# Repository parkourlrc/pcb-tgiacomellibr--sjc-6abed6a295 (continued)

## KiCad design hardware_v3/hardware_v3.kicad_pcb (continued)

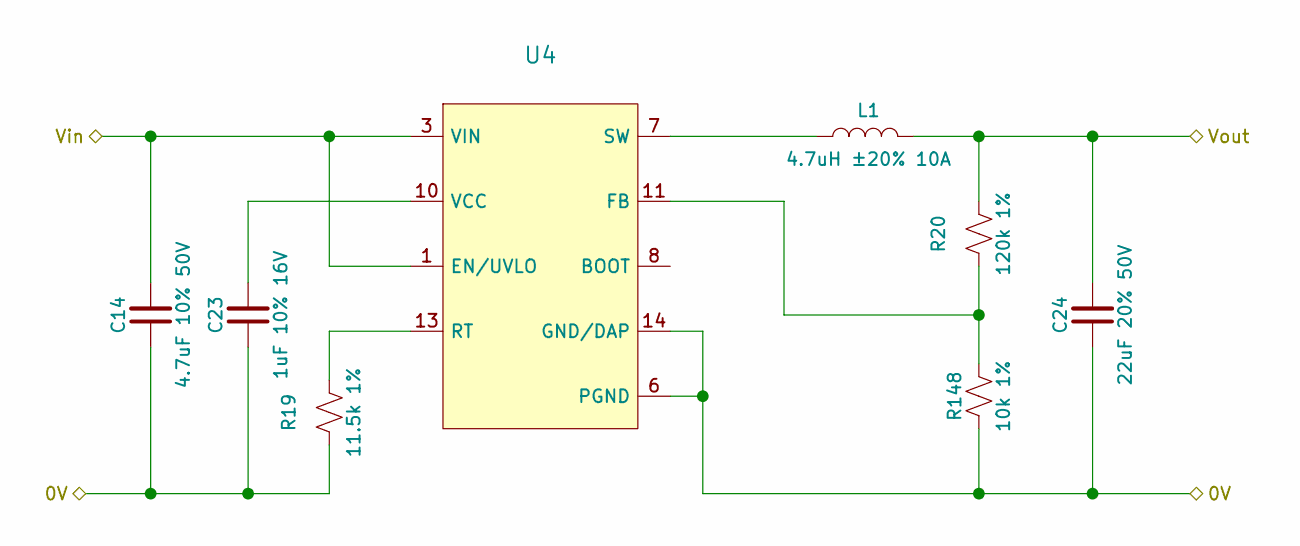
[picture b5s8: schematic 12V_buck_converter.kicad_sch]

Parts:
C14: 4.7uF 10% 50V; C_1206_3216Metric_Pad1.33x1.80mm_HandSolder; JLCPCB Part # C77096
C23: 1uF 10% 16V; C_0603_1608Metric_Pad1.08x0.95mm_HandSolder; JLCPCB Part # C92759
C24: 22uF 20% 50V; C_2220_5750Metric; JLCPCB Part # C2178233
L1: 4.7uH ±20% 10A; L_Vishay_IHLP-5050; JLCPCB Part # C845092
R19: 11.5k 1%; R_0603_1608Metric_Pad0.98x0.95mm_HandSolder; JLCPCB Part # C100728
R20: 120k 1%; R_0603_1608Metric_Pad0.98x0.95mm_HandSolder; JLCPCB Part # C114607
R148: 10k 1%; R_0603_1608Metric; JLCPCB Part # C98220
U4: (no value)

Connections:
+12V: C24.2, L1.2, R20.2; also elsewhere on the board
/Power Supply/12V_buck_converter/Vin: C14.2, U4.1 (EN/UVLO), U4.3 (VIN); also elsewhere on the board
unnamed: R20.1, R148.2, U4.11 (FB)
unnamed: U4.2 (NC), U4.4 (NC), U4.5 (NC), U4.9 (NC), U4.12 (NC)
unnamed: R19.2, U4.13 (RT)
unnamed: L1.1, U4.7 (SW)
unnamed: C23.2, U4.10 (VCC)
PGND: C14.1, C23.1, C24.1, R19.1, R148.1, U4.6 (PGND), U4.14 (GND/DAP); also elsewhere on the board

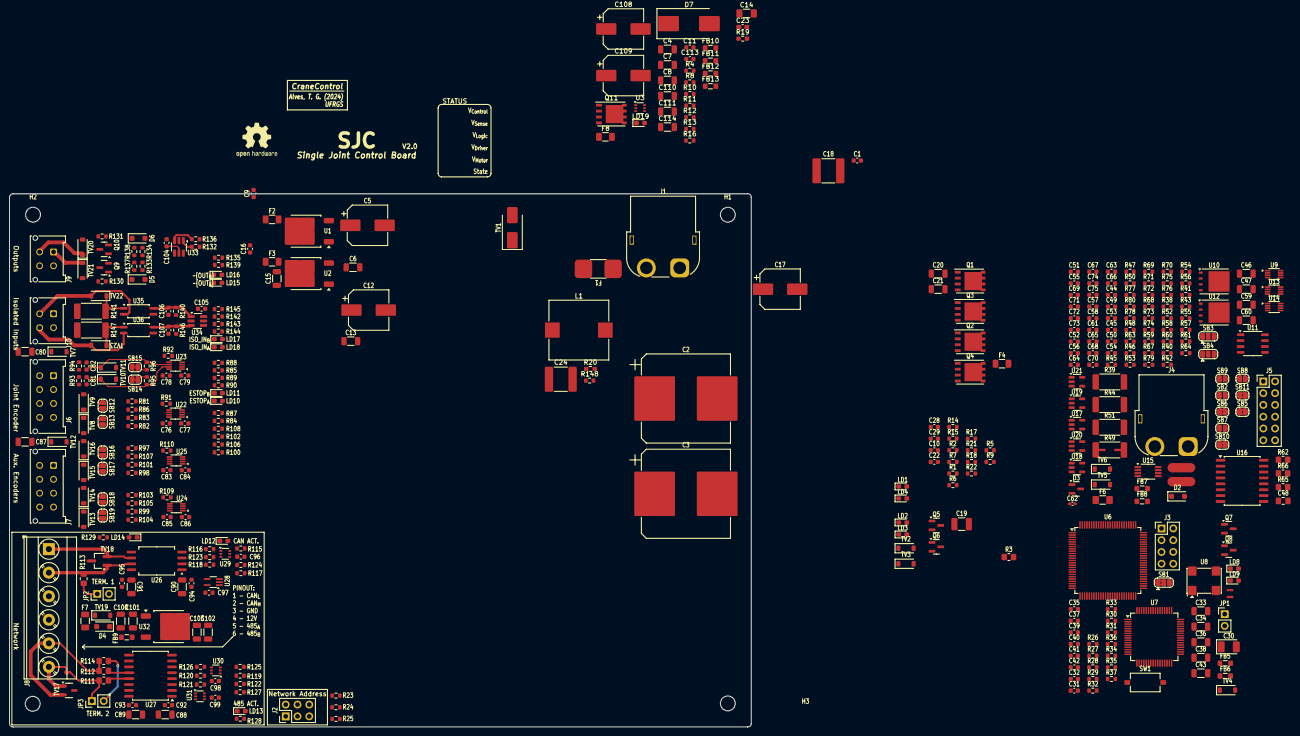
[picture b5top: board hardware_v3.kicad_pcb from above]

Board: 4 copper layers, 160.0 x 115.0 mm, 407 parts (0 on the bottom side), 255 nets.

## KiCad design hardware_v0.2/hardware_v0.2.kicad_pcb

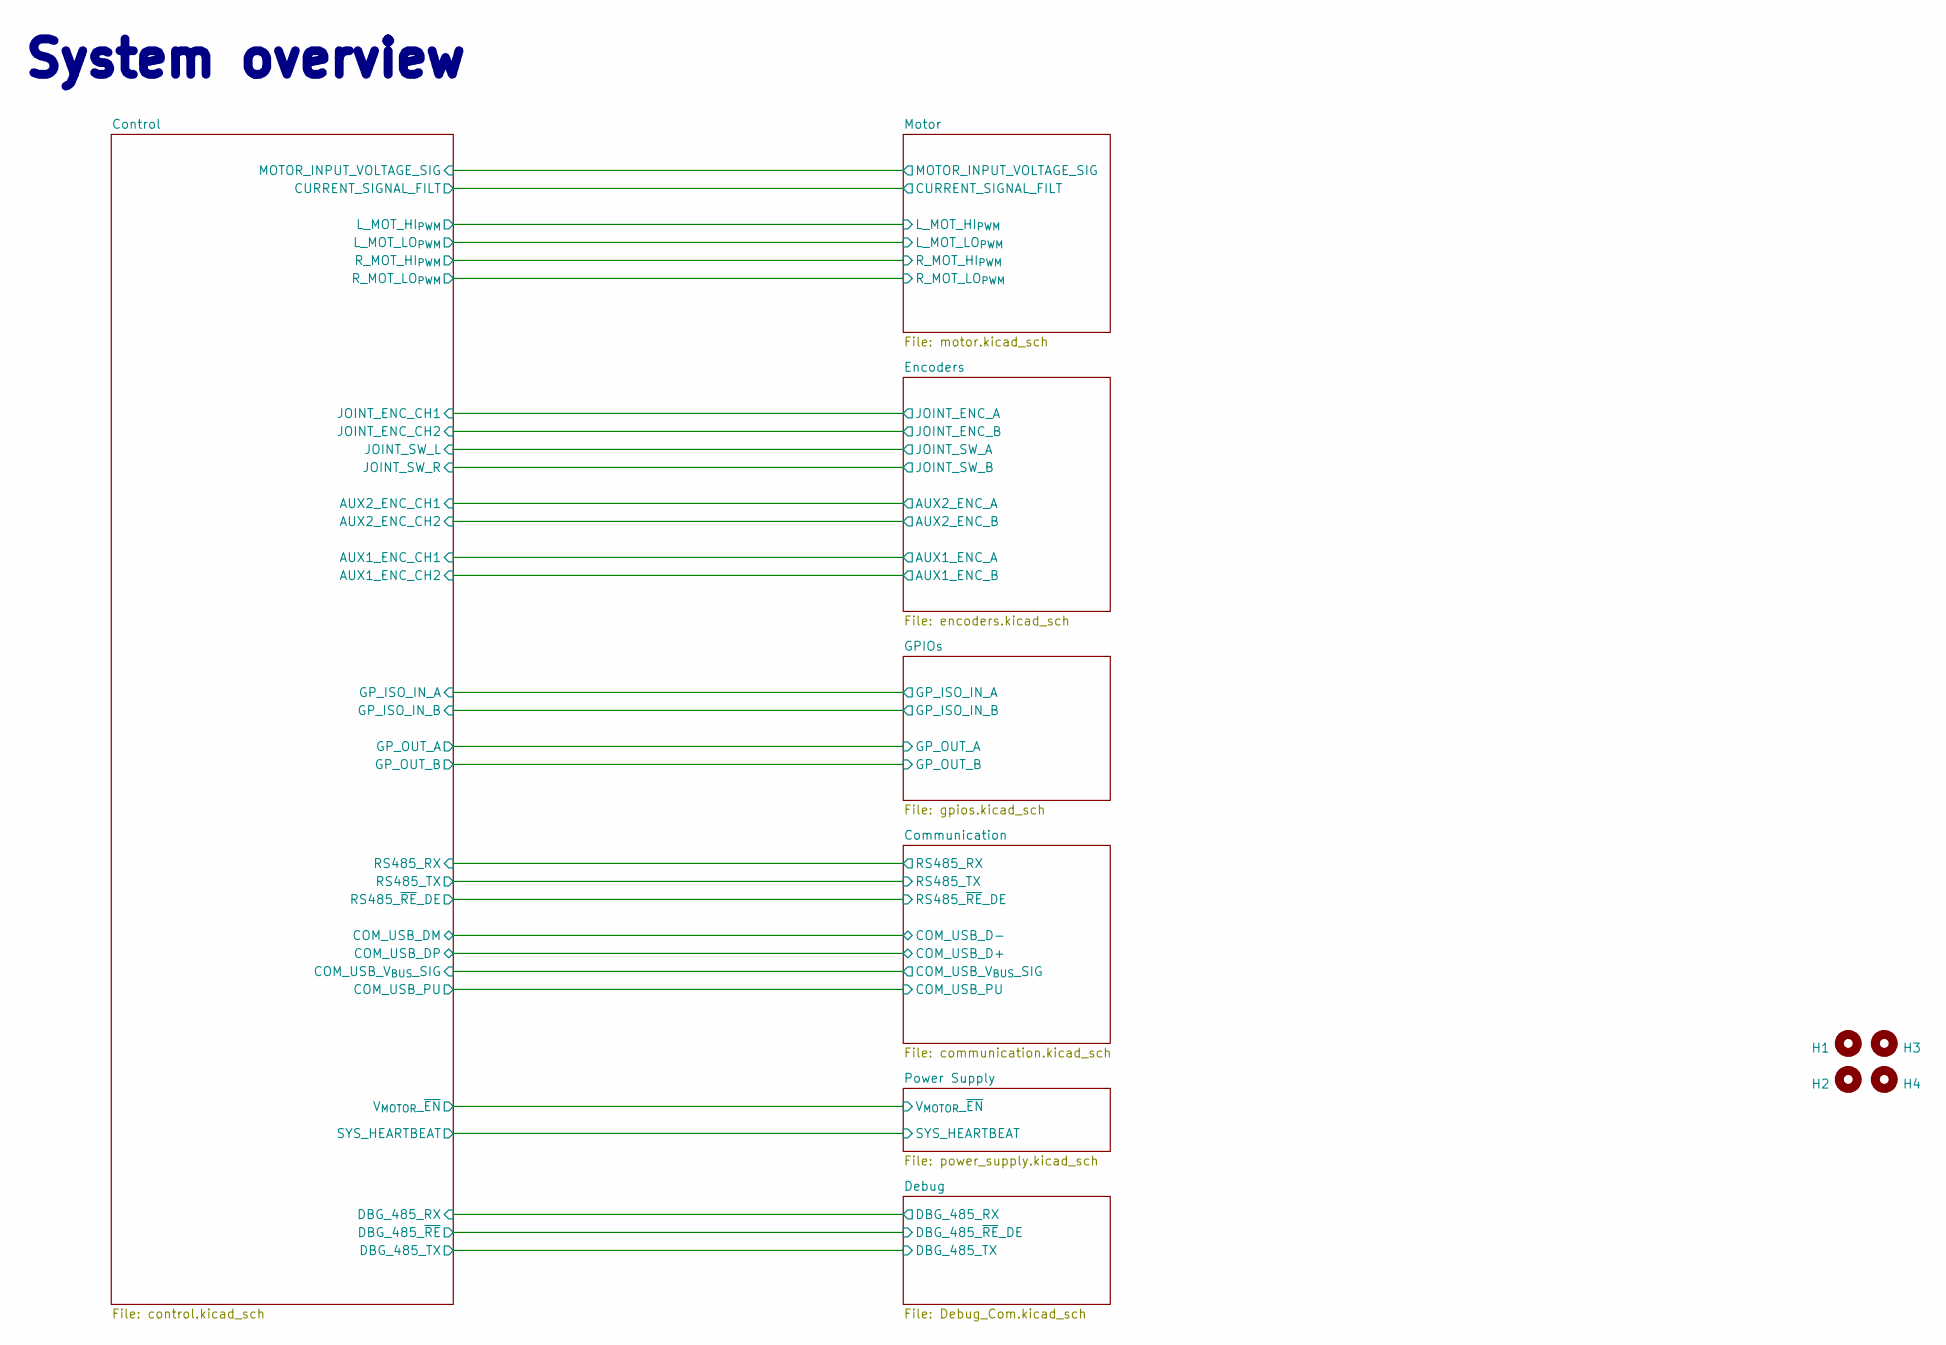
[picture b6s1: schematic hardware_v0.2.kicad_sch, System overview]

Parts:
H1, H2, H3, H4: MountingHole; MountingHole_3.2mm_M3_ISO7380

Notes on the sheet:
System overview

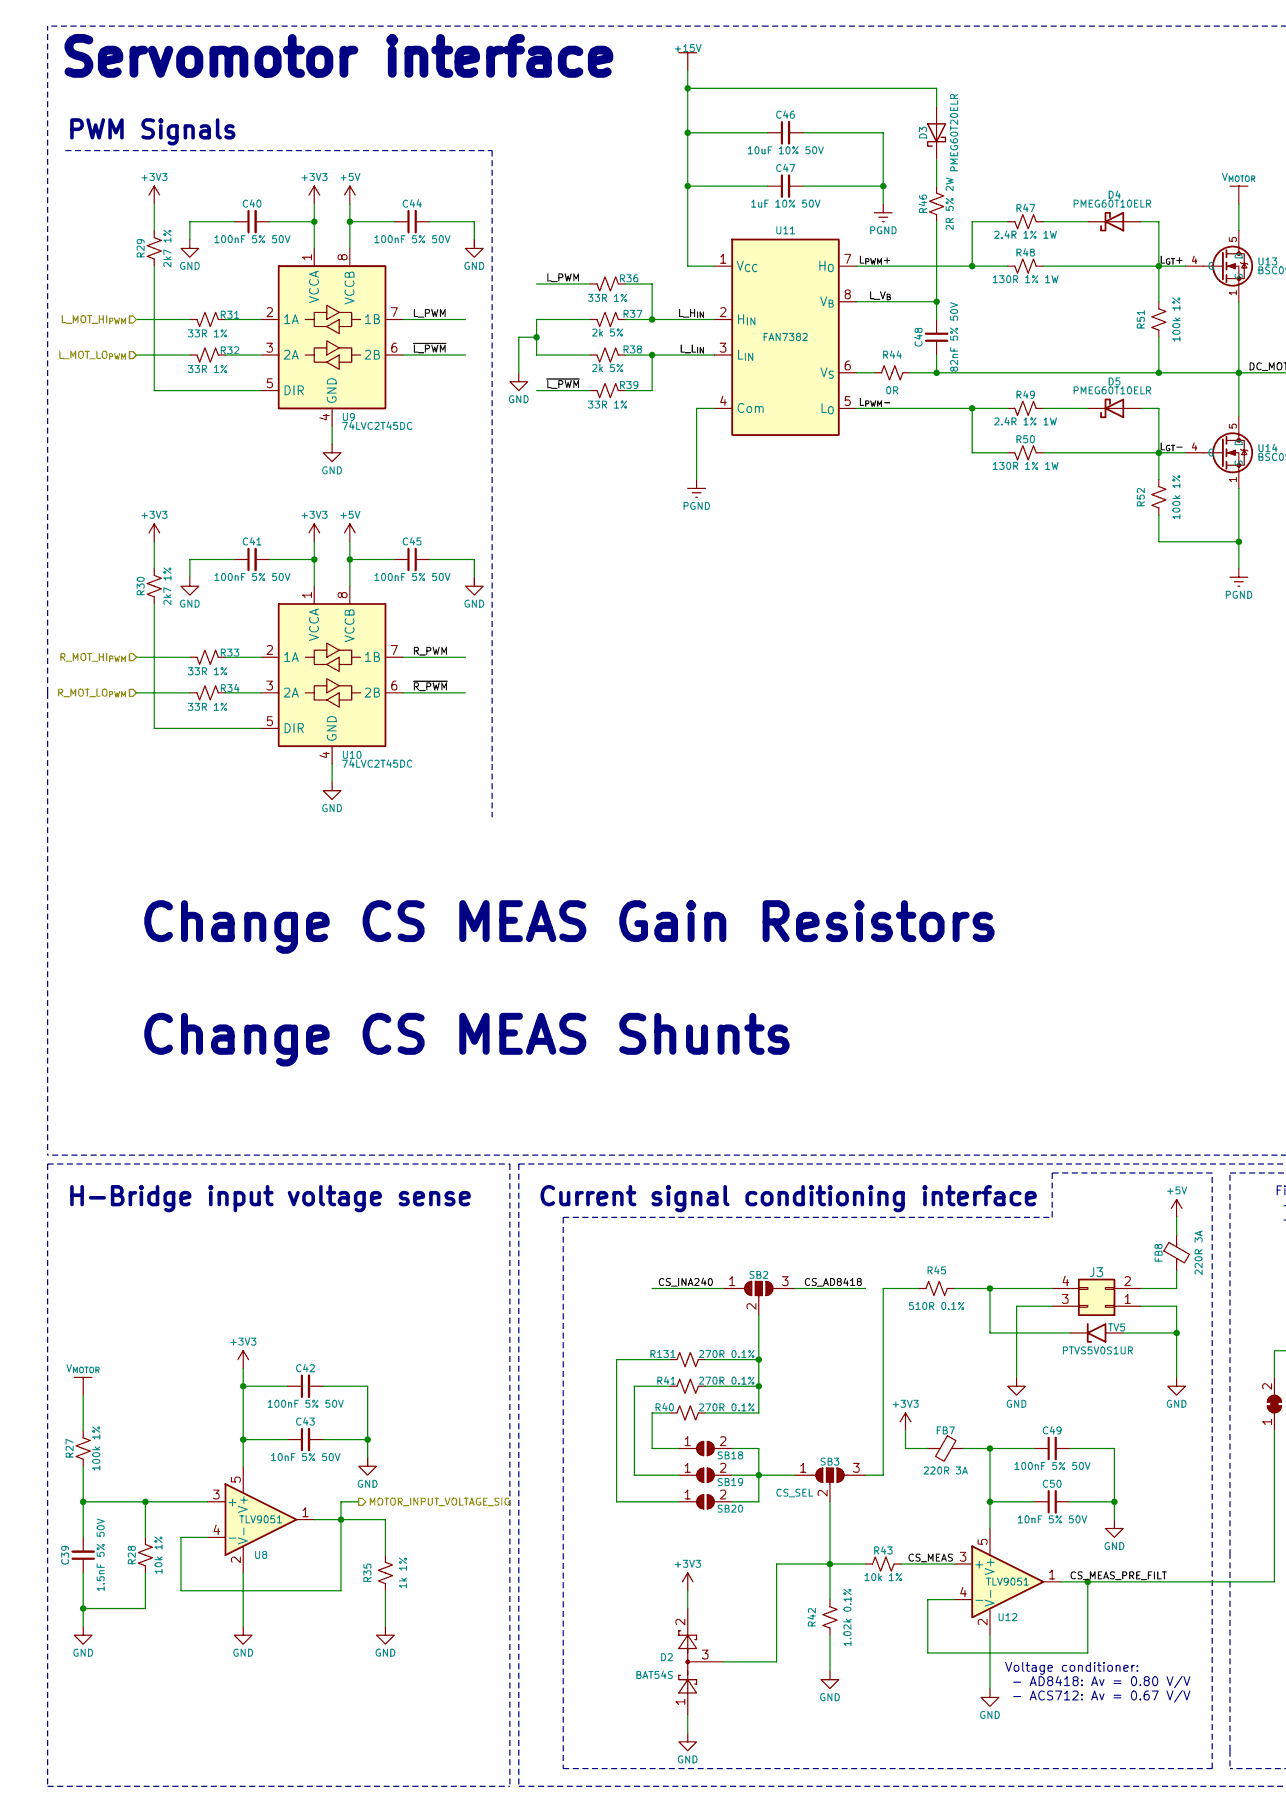
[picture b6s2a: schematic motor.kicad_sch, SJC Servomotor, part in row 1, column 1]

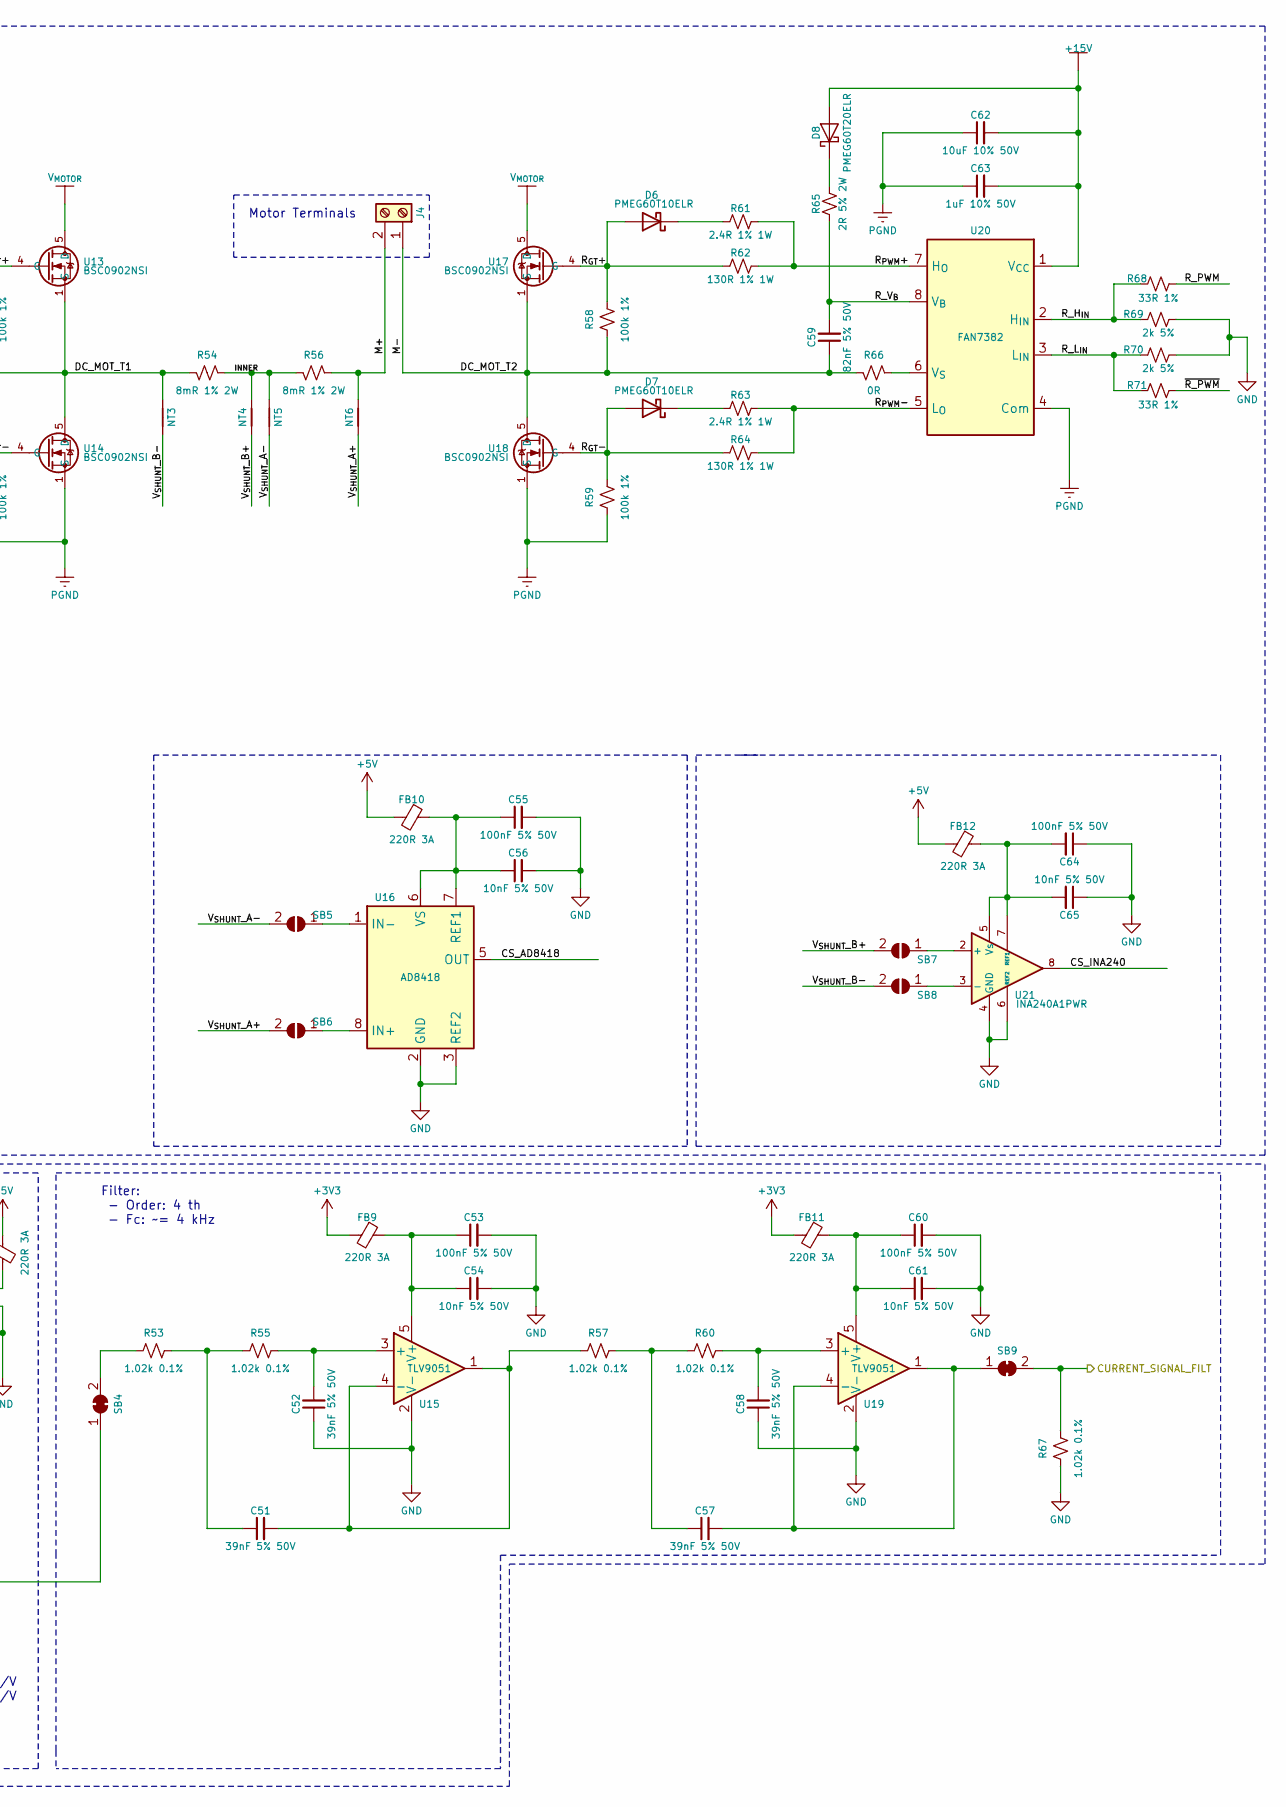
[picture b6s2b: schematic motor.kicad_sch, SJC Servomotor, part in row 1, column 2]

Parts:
C39: 1.5nF 5% 50V; C_0603_1608Metric; JLCPCB Part # C107039
C40, C41, C42, C44, C45, C49, C53, C55, C60, C64: 100nF 5% 50V; C_0603_1608Metric; JLCPCB Part # C91183
C43, C50, C54, C56, C61, C65: 10nF 5% 50V; C_0603_1608Metric; JLCPCB Part # C389113
C46, C62: 10uF 10% 50V; C_1206_3216Metric; JLCPCB Part # C13585
C47, C63: 1uF 10% 50V; C_1206_3216Metric; JLCPCB Part # C1848
C48, C59: 82nF 5% 50V; C_0805_2012Metric_Pad1.18x1.45mm_HandSolder; JLCPCB Part # C520047
C51, C52, C57, C58: 39nF 5% 50V; C_0603_1608Metric; JLCPCB Part # C519553
D2: BAT54S; SOT-23; JLCPCB Part # C19726
D3, D8: PMEG60T20ELR; D_SOD-123F; JLCPCB Part # C552947
D4, D5, D6, D7: PMEG60T10ELR; D_SOD-123F; JLCPCB Part # C552945
FB7, FB8, FB9, FB10, FB11, FB12: 220R 3A; L_0805_2012Metric_Pad1.05x1.20mm_HandSolder; JLCPCB Part # C76818
J3: Debug-485; PinHeader_2x02_P2.54mm_Vertical
J4: Motor; AMASS_XT60PW-M_1x02_P7.20mm_Horizontal; JLCPCB Part # C98732
NT3, NT5: SHUNT IN-; NetTie-2_SMD_Pad1.0mm
NT4, NT6: SHUNT IN+; NetTie-2_SMD_Pad1.0mm
R27, R51, R52, R58, R59: 100k 1%; R_0603_1608Metric; JLCPCB Part # C14675
R28, R43: 10k 1%; R_0603_1608Metric; JLCPCB Part # C98220
R29, R30: 2k7 1%; R_0603_1608Metric; JLCPCB Part # C114612
R31, R32, R33, R34, R36, R39, R68, R71: 33R 1%; R_0603_1608Metric; JLCPCB Part # C108661
R35: 1k 1%; R_0603_1608Metric; JLCPCB Part # C22548
R37, R38, R69, R70: 2k 5%; R_0603_1608Metric; JLCPCB Part # C103396
R40, R41, R131: 270R 0.1%; R_0603_1608Metric; JLCPCB Part # C861270
R42, R53, R55, R57, R60, R67: 1.02k 0.1%; R_0603_1608Metric; JLCPCB Part # C705819
R44, R66: 0R; R_0603_1608Metric; JLCPCB Part # C103196
R45: 510R 0.1%; R_0603_1608Metric; JLCPCB Part # C2828640
R46, R65: 2R 5% 2W; R_2512_6332Metric_Pad1.40x3.35mm_HandSolder; JLCPCB Part # C91926
R47, R49, R61, R63: 2.4R 1% 1W; R_2512_6332Metric_Pad1.40x3.35mm_HandSolder; JLCPCB Part # C175225
R48, R50, R62, R64: 130R 1% 1W; R_2512_6332Metric_Pad1.40x3.35mm_HandSolder; JLCPCB Part # C728111
R54, R56: 8mR 1% 2W; R_2512_6332Metric_Pad1.40x3.35mm_HandSolder; JLCPCB Part # C2440282
SB2, SB3: CS_SEL; SolderJumper-3_P1.3mm_Open_RoundedPad1.0x1.5mm
SB4, SB9: SolderJumper-2_P1.3mm_Bridged2Bar_RoundedPad1.0x1.5mm
SB5, SB6, SB7, SB8, SB18, SB19, SB20: SolderJumper-2_P1.3mm_Open_RoundedPad1.0x1.5mm
TV5: PTVS5V0S1UR; D_SOD-123; JLCPCB Part # C478011
U8, U12, U15, U19: TLV9051; SOT-23-5; JLCPCB Part # C1849429
U9, U10: 74LVC2T45DC; VSSOP-8_2.3x2mm_P0.5mm; JLCPCB Part # C730237
U11, U20: FAN7382; SOIC-8_3.9x4.9mm_P1.27mm; JLCPCB Part # C128796
U13, U14, U17, U18: BSC0902NSI; TDSON-8-1; JLCPCB Part # C534382
U16: AD8418; MSOP-8_3x3mm_P0.65mm; JLCPCB Part # C147928
U21: INA240A1PWR; TSSOP-8_4.4x3mm_P0.65mm; JLCPCB Part # C93965

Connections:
+3V3: C40.2, C41.2, C42.1, C43.1, D2.2, FB7.2, FB9.2, FB11.2, R29.2, R30.2, U8.5 (V+), U9.1 (VCCA), U10.1 (VCCA); also elsewhere on the board
+5V: C44.1, C45.1, FB8.1, FB10.2, FB12.2, U9.8 (VCCB), U10.8 (VCCB); also elsewhere on the board
+15V: C46.1, C47.1, C62.2, C63.2, D3.2 (A), D8.2 (A), U11.1 (V_{CC}), U20.1 (V_{CC}); also elsewhere on the board
/Control/CURRENT_SIGNAL_FILT: R67.2, SB9.2 (B); also elsewhere on the board
/Control/L_MOT_HI_{PWM}: R31.2; also elsewhere on the board
/Control/L_MOT_LO_{PWM}: R32.2; also elsewhere on the board
/Control/MOTOR_INPUT_VOLTAGE_SIG: R35.2, U8.1, U8.4 (-); also elsewhere on the board
/Control/R_MOT_HI_{PWM}: R33.2; also elsewhere on the board
/Control/R_MOT_LO_{PWM}: R34.2; also elsewhere on the board
/Motor/CS_MEAS: R43.2, U12.3 (+)
/Motor/CS_MEAS_PRE_FILT: SB4.1 (A), U12.1, U12.4 (-)
/Motor/DC_MOT_T1: C48.1, NT3.1, R44.2, R51.1, R54.2, U13.1 (S), U13.2 (S), U13.3 (S), U14.5 (D)
/Motor/DC_MOT_T2: C59.1, J4.1, R58.1, R66.2, U17.1 (S), U17.2 (S), U17.3 (S), U18.5 (D)
/Motor/INNER: NT4.1, NT5.1, R54.1, R56.2
/Motor/L_H_{IN}: R36.1, R37.1, U11.2 (H_{IN})
/Motor/L_L_{IN}: R38.1, R39.1, U11.3 (L_{IN})
/Motor/L_PWM: R36.2, U9.7 (1B)
/Motor/L_V_{B}: C48.2, R46.1, U11.8 (V_{B})
/Motor/L_{GT}+: D4.2 (A), R48.1, R51.2, U13.4 (G)
/Motor/L_{GT}-: D5.2 (A), R50.1, R52.2, U14.4 (G)
/Motor/L_{PWM}+: R47.2, R48.2, U11.7 (H_{O})
/Motor/L_{PWM}-: R49.2, R50.2, U11.5 (L_{O})
/Motor/M+: J4.2, NT6.1, R56.1
/Motor/R_H_{IN}: R68.1, R69.1, U20.2 (H_{IN})
/Motor/R_L_{IN}: R70.1, R71.1, U20.3 (L_{IN})
/Motor/R_PWM: R68.2, U10.7 (1B)
/Motor/R_V_{B}: C59.2, R65.1, U20.8 (V_{B})
/Motor/R_{GT}+: D6.2 (A), R58.2, R62.1, U17.4 (G)
/Motor/R_{GT}-: D7.2 (A), R59.2, R64.1, U18.4 (G)
/Motor/R_{PWM}+: R61.2, R62.2, U20.7 (H_{O})
/Motor/R_{PWM}-: R63.2, R64.2, U20.5 (L_{O})
/Motor/V_{SHUNT}_B+: NT4.2, SB7.1 (A), SB7.2 (B), U21.2 (+)
/Motor/V_{SHUNT}_B-: NT3.2, SB8.1 (A), SB8.2 (B), U21.3 (-)
/Motor/~L_PWM: R39.2, U9.6 (2B)
/Motor/~R_PWM: R71.2, U10.6 (2B)
GND: C39.1, C40.1, C41.1, C42.2, C43.2, C44.2, C45.2, C49.2, C50.2, C52.1, C53.2, C54.2, C55.2, C56.2, C58.1, C60.2, C61.2, C64.1, C65.1, D2.1, J3.1, J3.3, R28.1, R35.1, R37.2, R38.2, R42.1, R67.1, R69.2, R70.2, TV5.2 (A), U8.2 (V-), U9.4 (GND), U10.4 (GND), U12.2 (V-), U15.2 (V-), U16.2 (GND), U16.3 (REF2), U19.2 (V-), U21.1 (GND), U21.4 (GND), U21.6 (REF2); also elsewhere on the board
unnamed: C51.1, R53.2, R55.1
unnamed: C57.1, R57.2, R60.1
unnamed: D3.1 (K), R46.2
unnamed: D4.1 (K), R47.1
unnamed: D5.1 (K), R49.1
unnamed: D6.1 (K), R61.1
unnamed: D7.1 (K), R63.1
unnamed: D8.1 (K), R65.2
unnamed: FB8.2, J3.2
unnamed: J3.4, R45.2, TV5.1 (K)
unnamed: R40.1, R41.1, R131.1, SB2.2 (C)
unnamed: R45.1, SB3.3 (B)
unnamed: D2.3, R42.2, R43.1, SB3.2 (C)
unnamed: R53.1, SB4.2 (B)
unnamed: C57.2, SB9.1 (A), U19.1, U19.4 (-)
unnamed: R40.2, SB18.1 (A)
unnamed: SB3.1 (A), SB18.2 (B), SB19.2 (B), SB20.2 (B)
unnamed: R41.2, SB19.1 (A)
unnamed: R131.2, SB20.1 (A)
unnamed: C39.2, R27.1, R28.2, U8.3 (+)
unnamed: R31.1, U9.2 (1A)
unnamed: R32.1, U9.3 (2A)
unnamed: R29.1, U9.5 (DIR)
unnamed: R33.1, U10.2 (1A)
unnamed: R34.1, U10.3 (2A)
unnamed: R30.1, U10.5 (DIR)
unnamed: R44.1, U11.6 (V_{S})
unnamed: C49.1, C50.1, FB7.1, U12.5 (V+)
unnamed: C52.2, R55.2, U15.3 (+)
unnamed: C51.2, R57.1, U15.1, U15.4 (-)
unnamed: C53.1, C54.1, FB9.1, U15.5 (V+)
unnamed: C55.1, C56.1, FB10.1, U16.6 (VS), U16.7 (REF1)
unnamed: C58.2, R60.2, U19.3 (+)
unnamed: C60.1, C61.1, FB11.1, U19.5 (V+)
unnamed: R66.1, U20.6 (V_{S})
unnamed: C64.2, C65.2, FB12.1, U21.5 (Vs), U21.7 (REF1)
PGND: C46.2, C47.2, C62.1, C63.1, R52.1, R59.1, U11.4 (Com), U14.1 (S), U14.2 (S), U14.3 (S), U18.1 (S), U18.2 (S), U18.3 (S), U20.4 (Com); also elsewhere on the board
V_{MOTOR}: R27.2, U13.5 (D), U17.5 (D); also elsewhere on the board

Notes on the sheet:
Current signal conditioning interface
Servomotor interface
PWM Signals
Voltage conditioner: - AD8418: Av = 0.80 V/V - ACS712: Av = 0.67 V/V
Filter: - Order: 4 th - Fc: ~= 4 kHz
Change CS MEAS Gain Resistors Change CS MEAS Shunts
Motor Terminals
H-Bridge input voltage sense

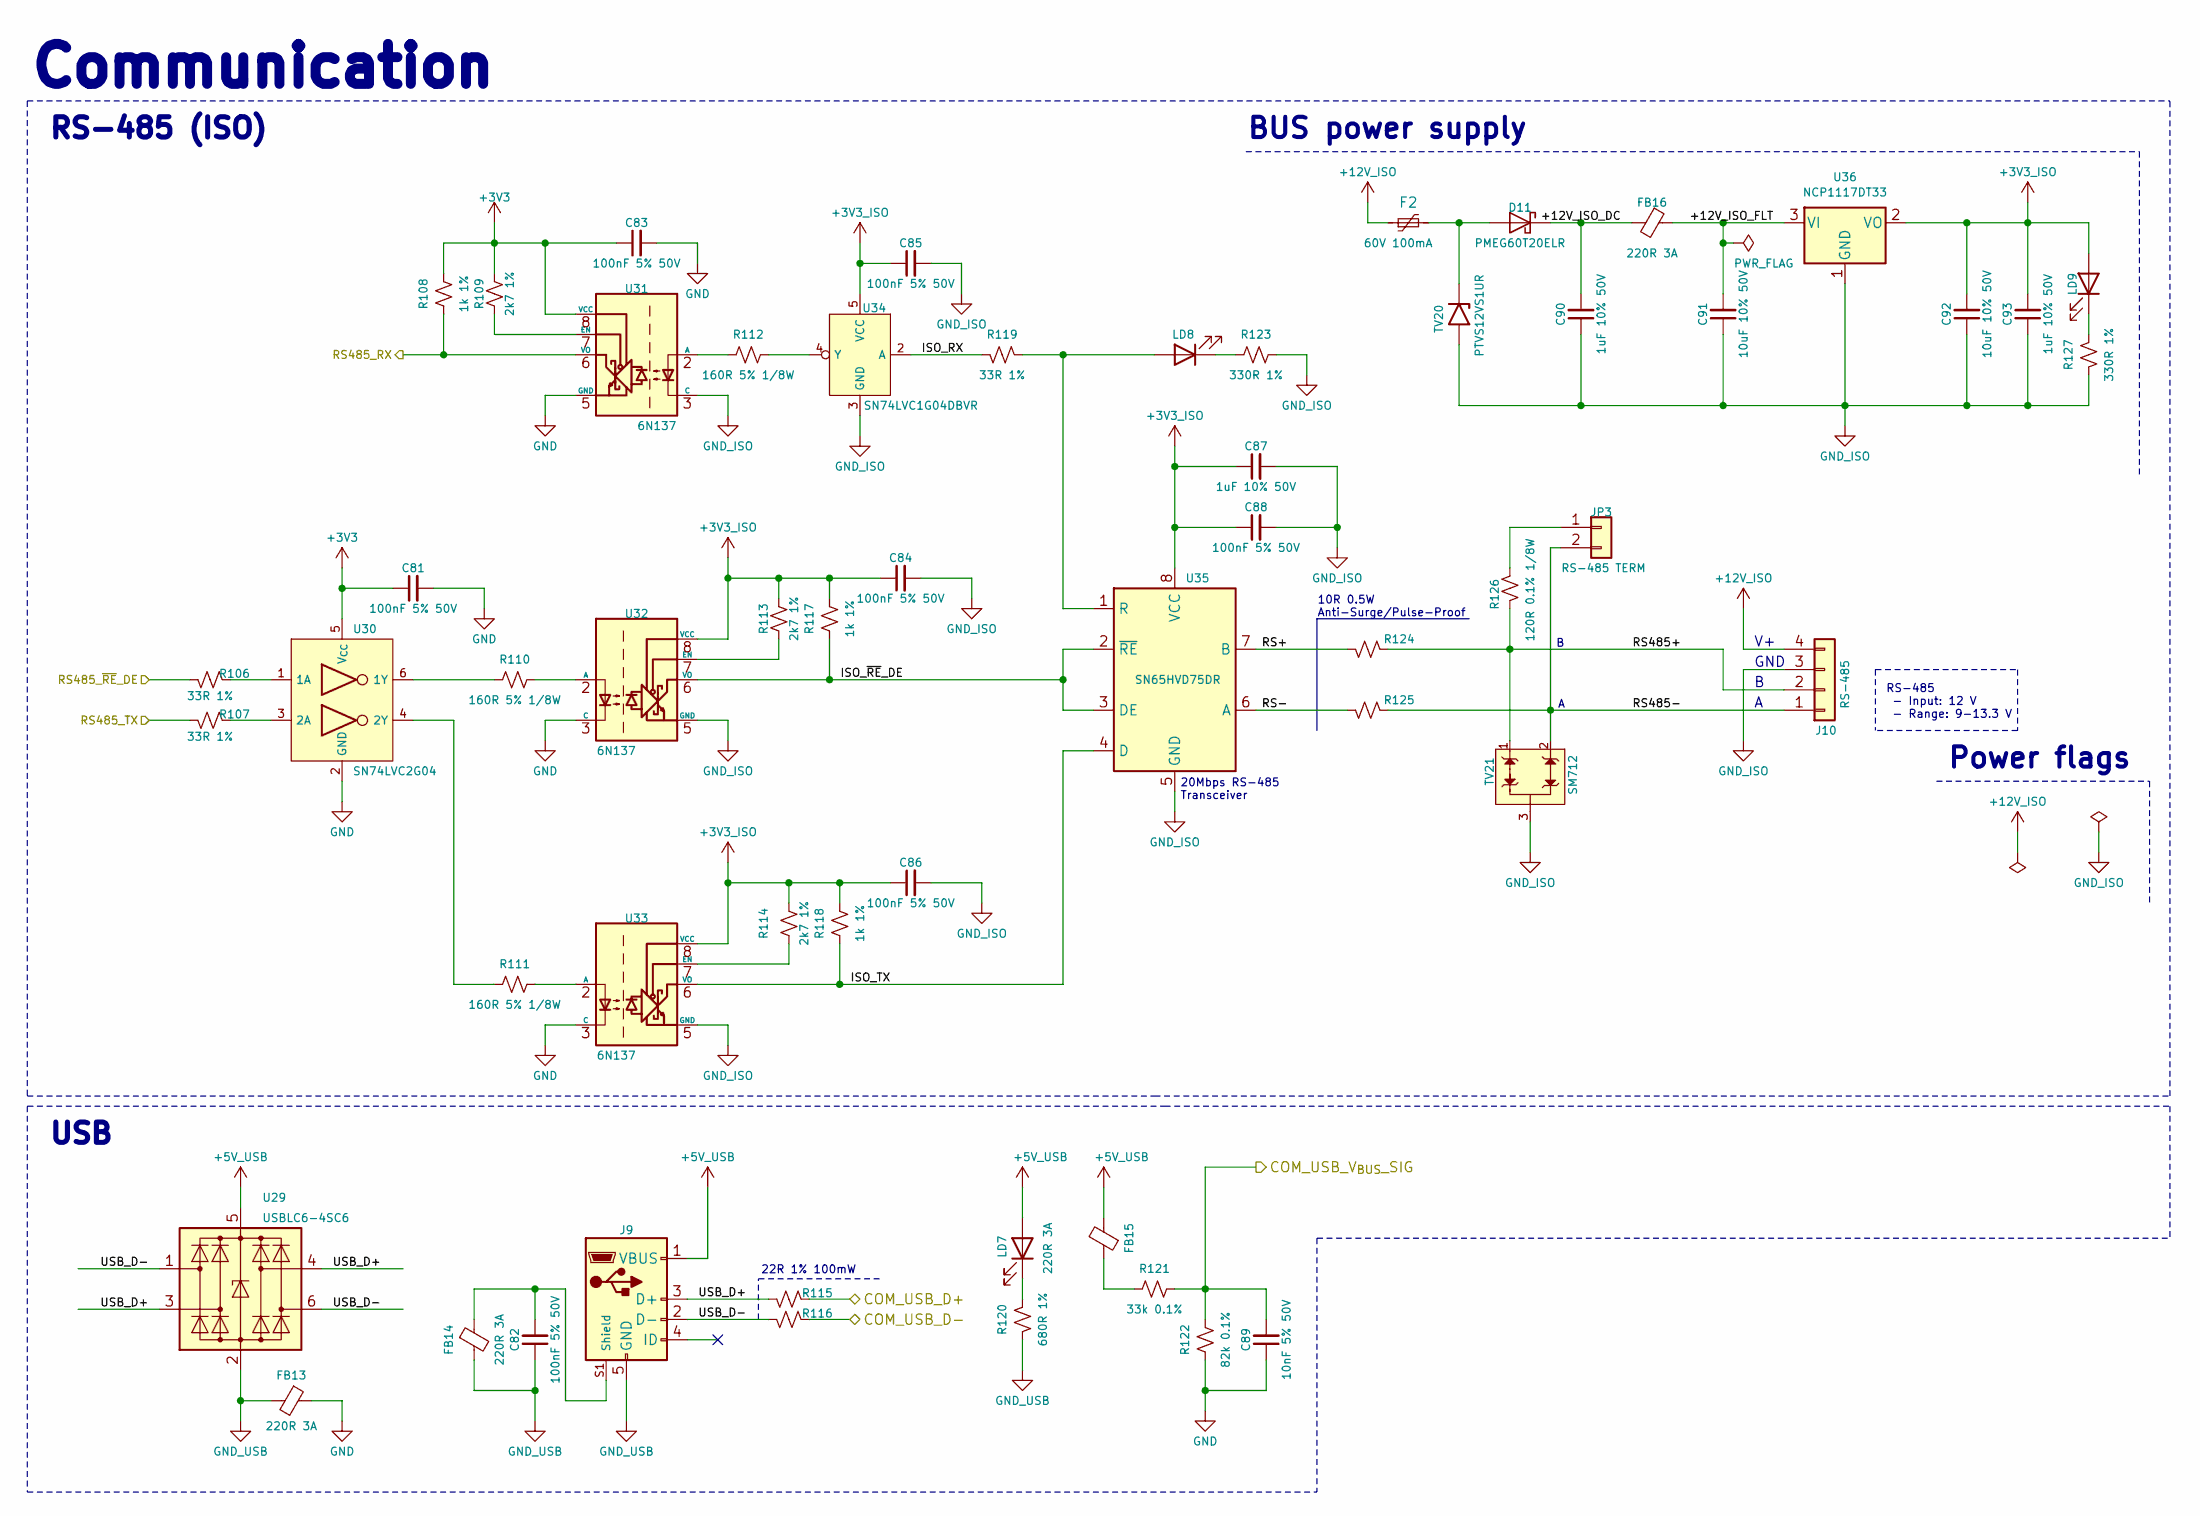
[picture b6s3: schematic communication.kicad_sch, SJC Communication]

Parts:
C81, C82, C83, C84, C85, C86, C88: 100nF 5% 50V; C_0603_1608Metric; JLCPCB Part # C91183
C87, C90, C93: 1uF 10% 50V; C_1206_3216Metric; JLCPCB Part # C1848
C89: 10nF 5% 50V; C_0603_1608Metric; JLCPCB Part # C389113
C91, C92: 10uF 10% 50V; C_1206_3216Metric; JLCPCB Part # C13585
D11: PMEG60T20ELR; D_SOD-123F; JLCPCB Part # C552947
F2: 60V 100mA; Fuse_1206_3216Metric; JLCPCB Part # C2153714
FB13, FB14, FB15, FB16: 220R 3A; L_0805_2012Metric_Pad1.05x1.20mm_HandSolder; JLCPCB Part # C76818
J9: AMPHENOL_10118194-0001LF; JLCPCB Part # C132563
J10: RS-485; TerminalBlock_Phoenix_MKDS-3-4-5.08_1x04_P5.08mm_Horizontal; JLCPCB Part # C2915641
JP3: RS-485 TERM; PinHeader_1x02_P2.54mm_Vertical; JLCPCB Part # C234182
LD7, LD8, LD9: 1.8V @ 5mA; LED_0603_1608Metric_Pad1.05x0.95mm_HandSolder; JLCPCB Part # C165982
R106, R107, R119: 33R 1%; R_0603_1608Metric; JLCPCB Part # C108661
R108, R117, R118: 1k 1%; R_0603_1608Metric; JLCPCB Part # C22548
R109, R113, R114: 2k7 1%; R_0603_1608Metric; JLCPCB Part # C114612
R110, R111, R112: 160R 5% 1/8W; R_0603_1608Metric; JLCPCB Part # C171721
R115, R116: 22R 1%; R_0603_1608Metric; JLCPCB Part # C107701
R120: 680R 1%; R_0603_1608Metric; JLCPCB Part # C2097840
R121: 33k 0.1%; R_0603_1608Metric; JLCPCB Part # C2828645
R122: 82k 0.1%; R_0603_1608Metric; JLCPCB Part # C728598
R123, R127: 330R 1%; R_0603_1608Metric; JLCPCB Part # C144102
R124, R125: 10R 1% 1/2W; R_0805_2012Metric_Pad1.20x1.40mm_HandSolder; JLCPCB Part # C441969
R126: 120R 0.1% 1/8W; R_0805_2012Metric_Pad1.20x1.40mm_HandSolder; JLCPCB Part # C2828708
TV20: PTVS12VS1UR; D_SOD-123; JLCPCB Part # C456115
TV21: SM712; SOT-23-3; JLCPCB Part # C293966
U29: USBLC6-4SC6; SOT-23-6_Handsoldering; JLCPCB Part # C111212
U30: SN74LVC2G04; SOT-23-6_Handsoldering; JLCPCB Part # C10428
U31, U32, U33: 6N137; SMDIP-8_W7.62mm; JLCPCB Part # C92651
U34: SN74LVC1G04DBVR; SOT-23-5_HandSoldering; JLCPCB Part # C7827
U35: SN65HVD75DR; SOIC-8_3.9x4.9mm_P1.27mm; JLCPCB Part # C57928
U36: NCP1117DT33; TO-252-2; JLCPCB Part # C152529

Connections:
+3V3: C81.1, C83.1, R108.2, R109.2, U30.5 (V_{CC}), U31.8 (VCC); also elsewhere on the board
+3V3_ISO: C84.1, C85.1, C86.1, C87.1, C88.1, C92.2, C93.2, LD9.2 (A), R113.2, R114.2, R117.2, R118.2, U32.8 (VCC), U33.8 (VCC), U34.5 (VCC), U35.8 (VCC), U36.2 (VO)
+5V_USB: FB15.2, J9.1 (VBUS), LD7.2 (A), U29.5 (VBUS)
+12V_ISO: F2.1, J10.4
/Communication/+12V_ISO_DC: C90.2, D11.1 (K), FB16.2
/Communication/+12V_ISO_FLT: C91.2, FB16.1, U36.3 (VI)
/Communication/COM_USB_D+: R115.1; also elsewhere on the board
/Communication/COM_USB_D-: R116.1; also elsewhere on the board
/Communication/COM_USB_V_{BUS}_SIG: C89.2, R121.2, R122.2; also elsewhere on the board
/Communication/ISO_RX: R119.2, U34.2 (A)
/Communication/ISO_TX: R118.1, U33.6 (VO), U35.4 (D)
/Communication/ISO_~RE_DE: R117.1, U32.6 (VO), U35.2 (~RE), U35.3 (DE)
/Communication/RS485+: J10.2, R124.1, R126.1, TV21.1
/Communication/RS485-: J10.1, JP3.2, R125.1, TV21.2
/Communication/RS485_RX: R108.1, U31.6 (VO); also elsewhere on the board
/Communication/RS485_TX: R107.2; also elsewhere on the board
/Communication/RS485_~RE_DE: R106.2; also elsewhere on the board
/Communication/RS+: R124.2, U35.7 (B)
/Communication/RS-: R125.2, U35.6 (A)
/Communication/USB_D+: J9.3 (D+), R115.2, U29.3 (I/O2), U29.4 (I/O3)
/Communication/USB_D-: J9.2 (D-), R116.2, U29.1 (I/O1), U29.6 (I/O4)
GND: C81.2, C83.2, C89.1, FB13.1, R122.1, U30.2 (GND), U31.5 (GND), U32.3 (C), U33.3 (C); also elsewhere on the board
GND_ISO: C84.2, C85.2, C86.2, C87.2, C88.2, C90.1, C91.1, C92.1, C93.1, J10.3, R123.2, R127.2, TV20.2 (A), TV21.3, U31.3 (C), U32.5 (GND), U33.5 (GND), U34.3 (GND), U35.5 (GND), U36.1 (GND)
GND_USB: C82.1, FB13.2, FB14.2, J9.5 (GND), R120.2, U29.2 (GND)
unnamed: C82.2, FB14.1, J9.S1 (Shield), J9.S2 (Shield), J9.S3 (Shield), J9.S4 (Shield), J9.S5 (Shield), J9.S6 (Shield)
unnamed: D11.2 (A), F2.2, TV20.1 (K)
unnamed: FB15.1, R121.1
unnamed: JP3.1, R126.2
unnamed: LD7.1 (K), R120.1
unnamed: LD8.2 (A), R119.1, U35.1 (R)
unnamed: LD8.1 (K), R123.1
unnamed: LD9.1 (K), R127.1
unnamed: R106.1, U30.1 (1A)
unnamed: R110.1, U30.6 (1Y)
unnamed: R107.1, U30.3 (2A)
unnamed: R111.1, U30.4 (2Y)
unnamed: R112.1, U31.2 (A)
unnamed: R109.1, U31.7 (EN)
unnamed: R110.2, U32.2 (A)
unnamed: R113.1, U32.7 (EN)
unnamed: R111.2, U33.2 (A)
unnamed: R114.1, U33.7 (EN)
unnamed: R112.2, U34.4 (Y)

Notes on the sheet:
RS-485 (ISO)
10R 0.5W Anti-Surge/Pulse-Proof
Power flags
20Mbps RS-485 Transceiver
BUS power supply
USB
22R 1% 100mW
GND
Communication
RS-485 - Input: 12 V - Range: 9-13.3 V
